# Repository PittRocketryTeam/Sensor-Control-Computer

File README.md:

# Sensor-Control-Computer
Code and design files for the Sensor and Control Avionics (SCA).

-`/hardware` contains Eagle schematics for SCA<br>
-`/software` contains software for SCA<br>

Current sensors:

- GPS: [Adafruit Ultimate GPS Breakout](https://www.adafruit.com/product/746) <br>
- Altimeter: [Adafruit BMP388](https://www.adafruit.com/product/3966) <br>
- IMU: [Adafruit 9-DOF Absolute Orientation IMU Fusion Breakout - BNO055](https://www.adafruit.com/product/2472) <br>
- Photocell: [CdS Photoresistor](https://www.adafruit.com/product/161) <br>
- Transceiver: [XBee Pro 900 HP](https://www.digikey.com/catalog/en/partgroup/xbee-pro-900hp/33082) <br>

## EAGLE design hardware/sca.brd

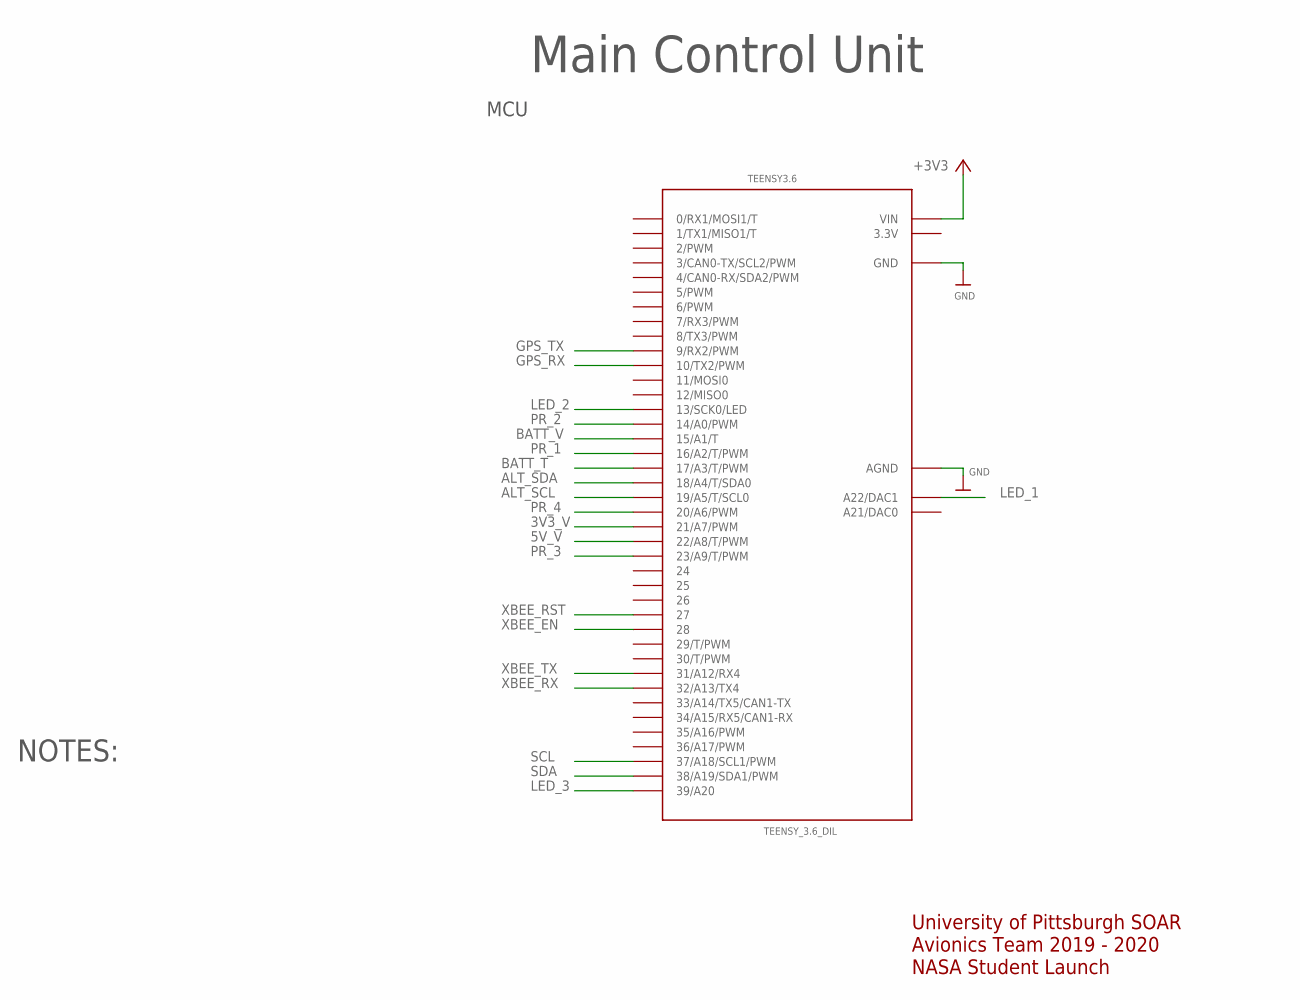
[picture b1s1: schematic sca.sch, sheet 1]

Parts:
TEENSY3.6: TEENSY_3.6_DIL

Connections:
3.3V: TEENSY3.6.3.3V, TEENSY3.6.3.3V3 (3.3V)
3V3_V: TEENSY3.6.21/A7 (21/A7/PWM); also elsewhere on the board
5V_V: TEENSY3.6.22/A8 (22/A8/T/PWM); also elsewhere on the board
+3V3: TEENSY3.6.VIN; also elsewhere on the board
ALT_SCL: TEENSY3.6.19/A5 (19/A5/T/SCL0); also elsewhere on the board
ALT_SDA: TEENSY3.6.18/A4 (18/A4/T/SDA0); also elsewhere on the board
BATT_T: TEENSY3.6.17/A3 (17/A3/T/PWM); also elsewhere on the board
BATT_V: TEENSY3.6.15/A1 (15/A1/T); also elsewhere on the board
GND: TEENSY3.6.AGND, TEENSY3.6.GND, TEENSY3.6.GND1 (GND); also elsewhere on the board
GPS_RX: TEENSY3.6.10 (10/TX2/PWM); also elsewhere on the board
GPS_TX: TEENSY3.6.9 (9/RX2/PWM); also elsewhere on the board
LED_1: TEENSY3.6.A22 (A22/DAC1); also elsewhere on the board
LED_2: TEENSY3.6.13 (13/SCK0/LED); also elsewhere on the board
LED_3: TEENSY3.6.39/A20; also elsewhere on the board
PR_1: TEENSY3.6.16/A2 (16/A2/T/PWM); also elsewhere on the board
PR_2: TEENSY3.6.14/A0 (14/A0/PWM); also elsewhere on the board
PR_3: TEENSY3.6.23/A9 (23/A9/T/PWM); also elsewhere on the board
PR_4: TEENSY3.6.20/A6 (20/A6/PWM); also elsewhere on the board
SCL: TEENSY3.6.37/A18 (37/A18/SCL1/PWM); also elsewhere on the board
SDA: TEENSY3.6.38/A19 (38/A19/SDA1/PWM); also elsewhere on the board
XBEE_EN: TEENSY3.6.28; also elsewhere on the board
XBEE_RST: TEENSY3.6.27; also elsewhere on the board
XBEE_RX: TEENSY3.6.32/A13 (32/A13/TX4); also elsewhere on the board
XBEE_TX: TEENSY3.6.31/A12 (31/A12/RX4); also elsewhere on the board

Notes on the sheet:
University of Pittsburgh SOAR Avionics Team 2019 - 2020 NASA Student Launch
NOTES:
Main Control Unit
MCU

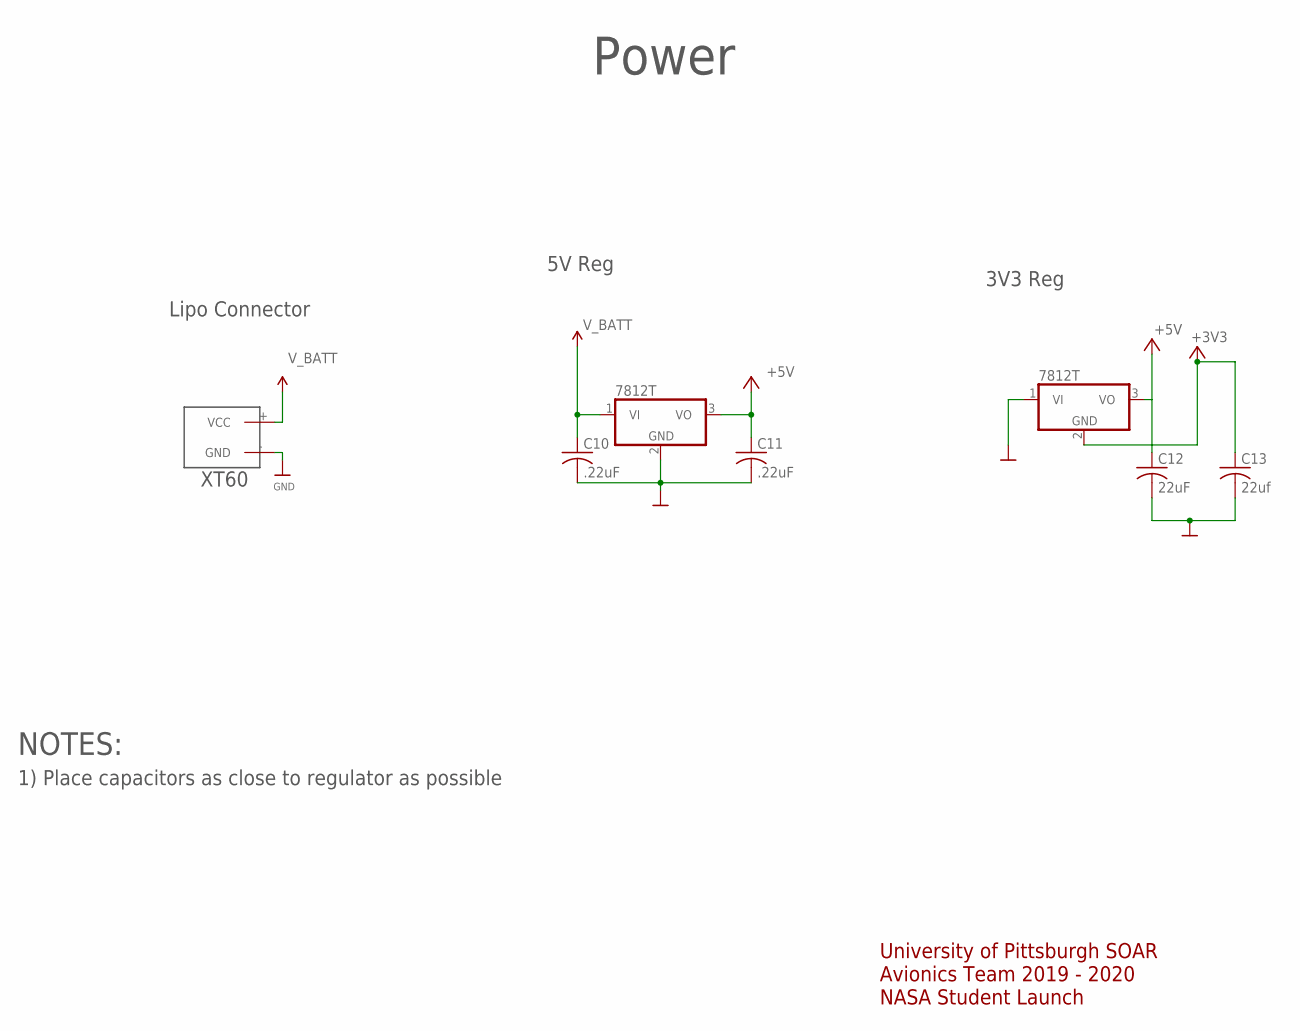
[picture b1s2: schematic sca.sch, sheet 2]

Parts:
3V3_REG, 5V_REG: 7812T; TO220H
C10, C11: .22uF; C025-040X050
C12: 22uF; C025-040X050
C13: 22uf; C025-040X050
U$5: XT60

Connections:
+3V3: 3V3_REG.2 (GND), C13.1; also elsewhere on the board
+5V: 3V3_REG.3 (VO), 5V_REG.3 (VO), C11.1, C12.1; also elsewhere on the board
GND: 3V3_REG.1 (VI), 5V_REG.2 (GND), C10.2, C11.2, C12.2, C13.2, U$5.- (GND); also elsewhere on the board
V_BATT: 5V_REG.1 (VI), C10.1, U$5.+ (VCC); also elsewhere on the board

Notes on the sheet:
Power
NOTES:
1) Place capacitors as close to regulator as possible
University of Pittsburgh SOAR Avionics Team 2019 - 2020 NASA Student Launch
Lipo Connector
5V Reg
3V3 Reg

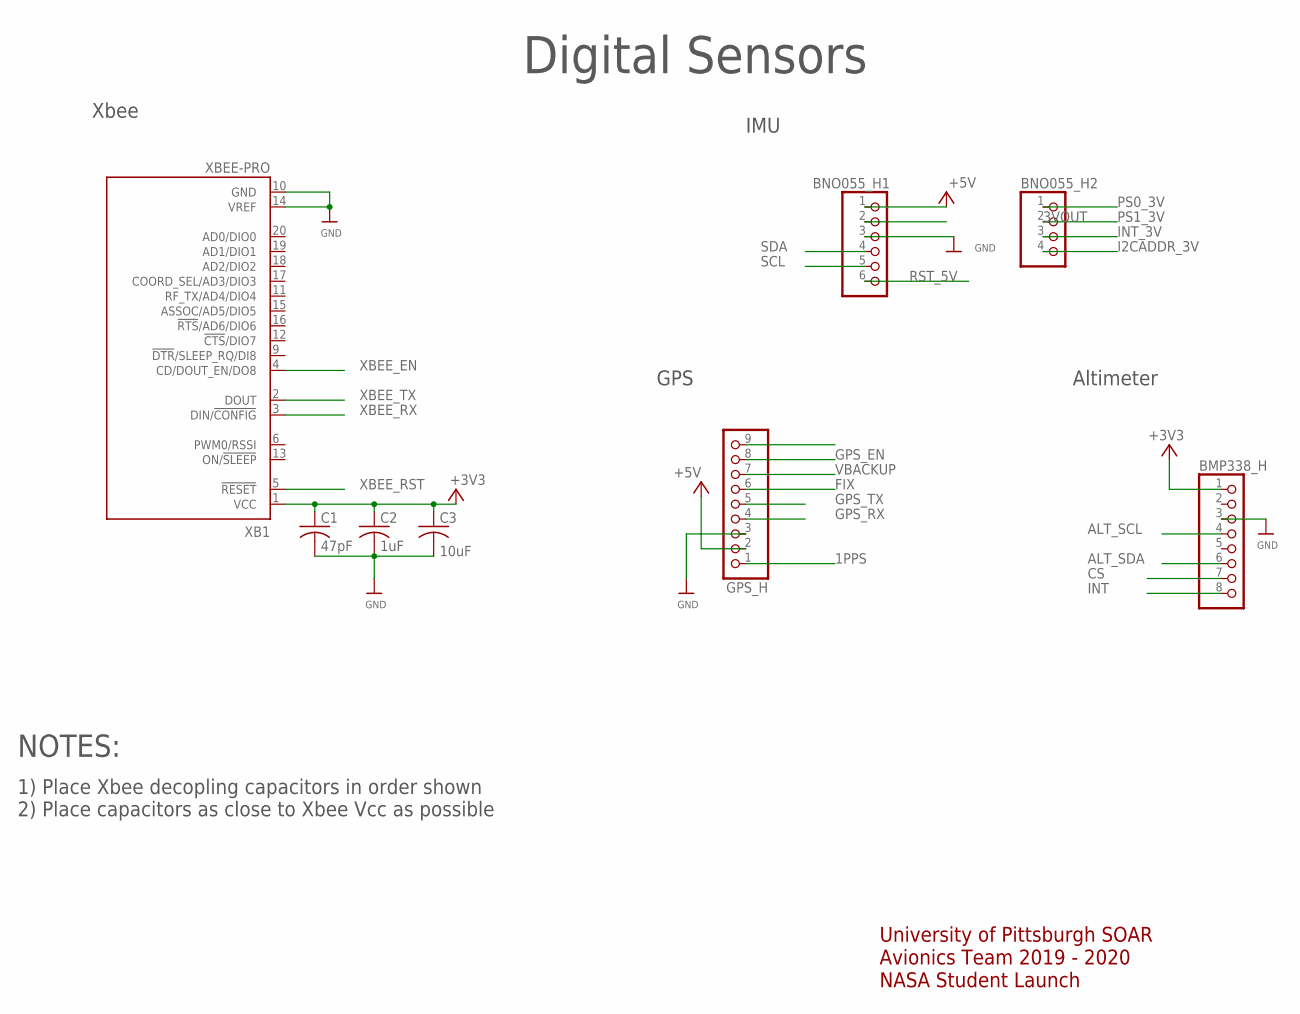
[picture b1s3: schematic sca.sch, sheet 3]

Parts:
BMP338_H: HEADER-1X870MIL; 1X08_ROUND_70
BNO055_H1: HEADER-1X676MIL; 1X06_ROUND_76
BNO055_H2: HEADER-1X476MIL; 1X04_ROUND_76
C1: 47pF; C025-040X050
C2: 1uF; C025-040X050
C3: 10uF; C025-040X050
GPS_H: HEADER-1X970MIL; 1X09_ROUND_70
XB1: XBEE-PRO

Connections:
1PPS: GPS_H.1
3VOUT: BNO055_H1.2
+3V3: BMP338_H.1, C1.1, C2.1, C3.1, XB1.1 (VCC); also elsewhere on the board
+5V: BNO055_H1.1, GPS_H.2; also elsewhere on the board
ALT_SCL: BMP338_H.4; also elsewhere on the board
ALT_SDA: BMP338_H.6; also elsewhere on the board
CS: BMP338_H.7
FIX: GPS_H.6
GND: BMP338_H.3, BNO055_H1.3, C1.2, C2.2, C3.2, GPS_H.3, XB1.10 (GND), XB1.14 (VREF); also elsewhere on the board
GPS_EN: GPS_H.8
GPS_RX: GPS_H.4; also elsewhere on the board
GPS_TX: GPS_H.5; also elsewhere on the board
I2CADDR_3V: BNO055_H2.4
INT: BMP338_H.8
INT_3V: BNO055_H2.3
PS0_3V: BNO055_H2.1
PS1_3V: BNO055_H2.2
RST_5V: BNO055_H1.6
SCL: BNO055_H1.5; also elsewhere on the board
SDA: BNO055_H1.4; also elsewhere on the board
VBACKUP: GPS_H.7
XBEE_EN: XB1.4 (CD/DOUT_EN/DO8); also elsewhere on the board
XBEE_RST: XB1.5 (!RESET); also elsewhere on the board
XBEE_RX: XB1.3 (DIN/!CONFIG); also elsewhere on the board
XBEE_TX: XB1.2 (DOUT); also elsewhere on the board

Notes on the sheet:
Digital Sensors
NOTES:
1) Place Xbee decopling capacitors in order shown 2) Place capacitors as close to Xbee Vcc as possible
University of Pittsburgh SOAR Avionics Team 2019 - 2020 NASA Student Launch
Xbee
IMU
GPS
Altimeter

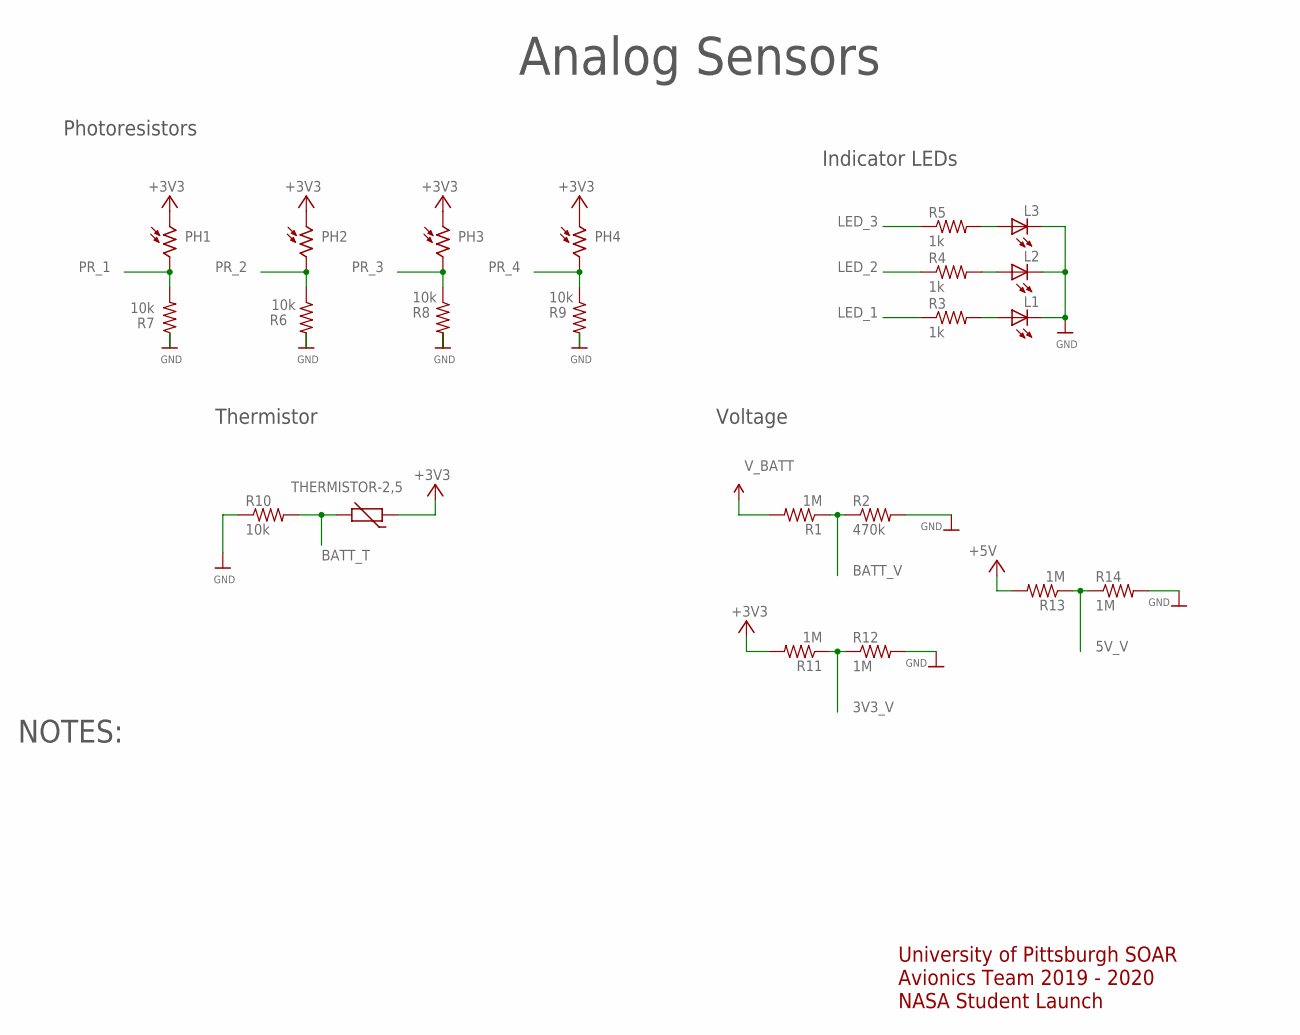
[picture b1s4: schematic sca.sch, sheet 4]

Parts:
L1, L2, L3: LED3MM
PH1, PH2, PH3, PH4: A1050_09; T0-46-A10XX
R1, R11, R12, R13, R14: 1M; 0309/10
R2: 470k; 0309/10
R3, R4, R5: 1k; 0309/10
R6, R7, R8, R9, R10: 10k; 0309/10
R20: THERMISTOR-2,5; RS-2,5

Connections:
3V3_V: R11.1, R12.1; also elsewhere on the board
5V_V: R13.1, R14.1; also elsewhere on the board
+3V3: PH1.1, PH2.1, PH3.1, PH4.1, R11.2, R20.1; also elsewhere on the board
+5V: R13.2; also elsewhere on the board
BATT_T: R10.2, R20.2; also elsewhere on the board
BATT_V: R1.1, R2.1; also elsewhere on the board
GND: L1.K (C), L2.K (C), L3.K (C), R2.2, R6.2, R7.1, R8.2, R9.2, R10.1, R12.2, R14.2; also elsewhere on the board
LED_1: R3.1; also elsewhere on the board
LED_2: R4.1; also elsewhere on the board
LED_3: R5.1; also elsewhere on the board
unnamed: L1.A, R3.2
unnamed: L2.A, R4.2
unnamed: L3.A, R5.2
PR_1: PH1.2, R7.2; also elsewhere on the board
PR_2: PH2.2, R6.1; also elsewhere on the board
PR_3: PH3.2, R8.1; also elsewhere on the board
PR_4: PH4.2, R9.1; also elsewhere on the board
V_BATT: R1.2; also elsewhere on the board

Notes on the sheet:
Analog Sensors
NOTES:
University of Pittsburgh SOAR Avionics Team 2019 - 2020 NASA Student Launch
Photoresistors
Thermistor
Voltage
Indicator LEDs

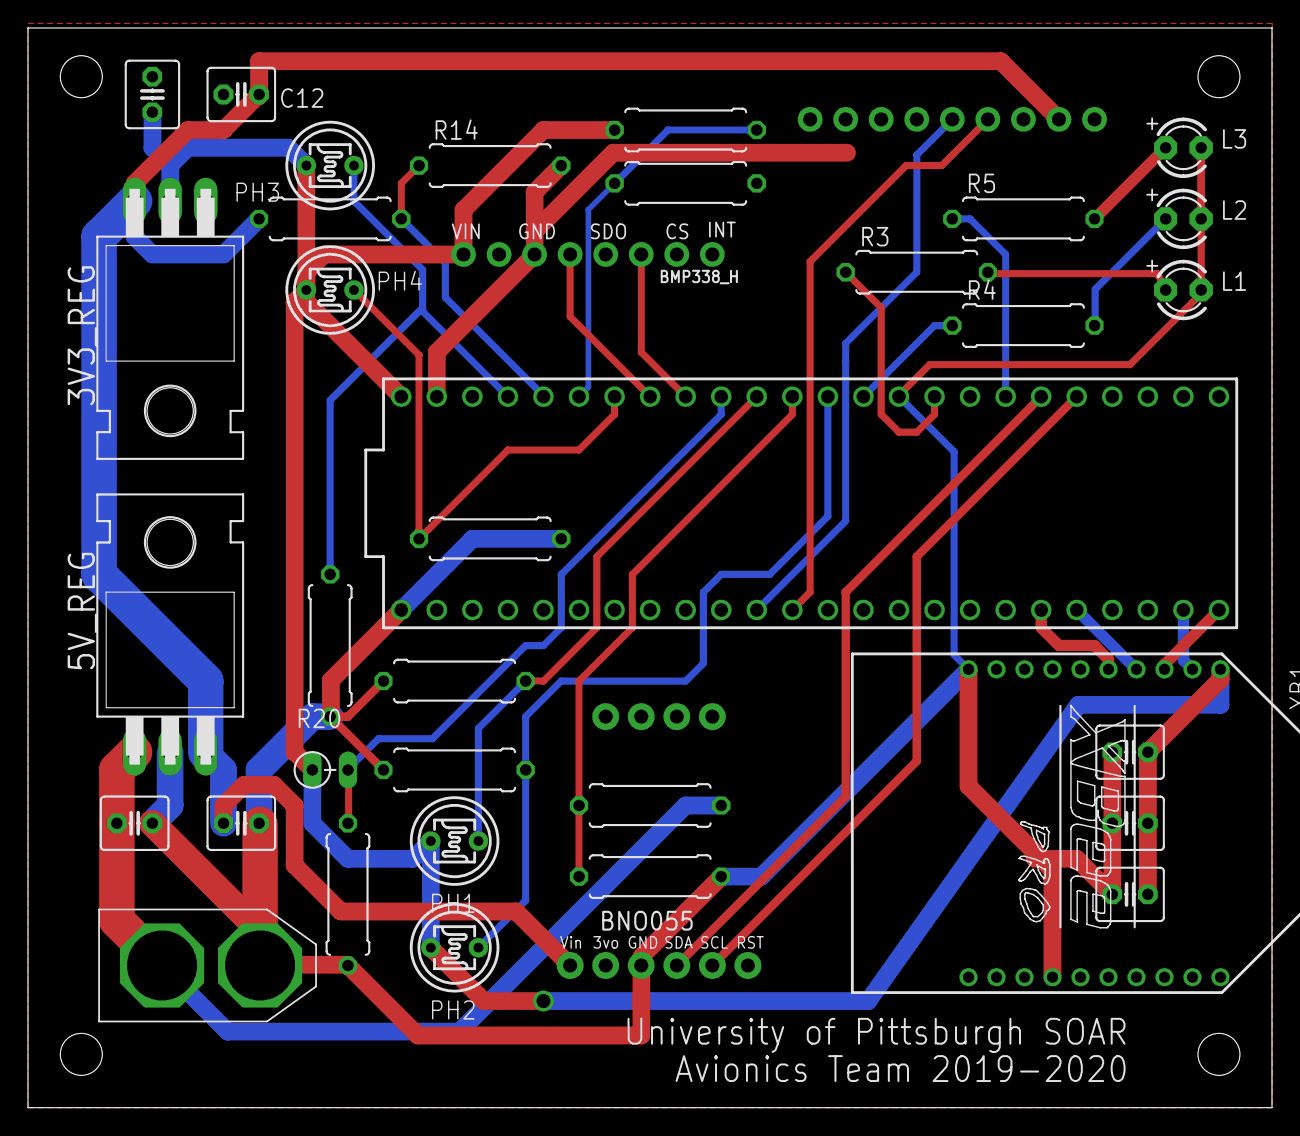
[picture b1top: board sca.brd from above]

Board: 2 copper layers, 88.9 x 77.1 mm, 38 parts (1 on the bottom side), 29 nets.

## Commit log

2019-09-23 add platformio project structure
2019-09-23 Updated readme and gitignore
2019-09-23 Moved existing software to software directory and created hardware directory
2019-09-23 moved autogenerated ci yaml file to /software
2019-09-29 Added schematic with teensy 3.6, XBee, BNO055 imu, Adafruit breakout GPS, and voltage dividers
2019-09-29 Added 4x photoresistors
2019-09-29 Added bmp388
2019-09-29 added thermistor circuit
2019-10-01 Created initial project structure as per inheritance meeting on sept 29
2019-10-01 Added source files for other components
2019-10-01 Made Sensor class functions non-pure so logger can add sensor-derived objects to collection of loggers
2019-10-01 Made logger functions non-pure (logger should be instantiable) and made addSensor use pass-by-pointer
2019-10-01 Fixed include guards
2019-10-01 Outlined remaining sensor and transceiver classes
2019-10-02 Added c++11 build flag, added GPS class, renamed transceiver write function to transmit and read function to receive
2019-10-03 Consolidated breakouts and added LEDs and battery voltage circuit
2019-10-03 added frame and cleaned up
2019-10-03 forgot to save last time
2019-10-03 added XT60 connector
2019-10-03 started power routing
2019-10-04 added thermistor routing
2019-10-06 add super constructor calls
2019-10-06 joe branch from master
2019-10-06 add metro library
2019-10-06 add atmega2560 env and implement health class
2019-10-07 Added data structs for altimeter, GPS, IMU, and photocell
2019-10-07 Removed unnecessary globals and created health class
2019-10-07 Resolve Health.cpp merge and updated readme with sensors
2019-10-07 Readme.md
2019-10-07 Changed vectors to structs; created preliminary logger class
2019-10-09 getting readings from sensor, testing different readings
2019-10-09 Changed SD to SdFat (faster logging), updated sensor functions to edit a struct rather than creating a new data struct, and added comments in sensor implementing classes to define what to do
2019-10-10 Added health data struct
2019-10-10 made changes discussed on Sunday
    temp sensor to 3V3
    photoresistors to 3V3
2019-10-10 Adding Adafruit Altimeter Library
2019-10-10 lots of layout changes
    updated teensy footprint to get rid of internal pins and pads
2019-10-11 Added EAGLE auto save and job file extensions
2019-10-11 missed one
2019-10-11 initial routing / changed xbee tx/rx for routing reasons
2019-10-11 Created a new function; added the 'setBaslinePressure' to the class file
2019-10-11 routing...
2019-10-11 Filled init, read, and baseline pressure(ground pressure)
2019-10-11 preliminary routing done
    adjusted some pins to optimize routing
2019-10-11 quick and dirty examples
2019-10-11 get_raw
2019-10-11 Updated poll() to just read the data
2019-10-11 implement Health and more examples
2019-10-11 cleaned up metro and added a few features
2019-10-12 Filled the enable, disable functions, and edited the read function so it wouldn't call 'performReading' twice
2019-10-12 fixed missed trace
2019-10-12 Added LoRa library
2019-10-13 Removed LoRa libary
2019-10-13 removed IMU 3V3 output
2019-10-13 added Xbee EN and Vref
2019-10-13 Added Decoupling Caps for Xbee per datasheet
2019-10-13 added notes
2019-10-13 added 3.3 and 5 V dividers
2019-10-13 Updated PDF
2019-10-13 Enable and disable
2019-10-13 Filled in init(), receive(),transmit(),enable(), and disable()
2019-10-13 spadinja/LoRaTransceiver: Minor change to enable()
2019-10-13 Added wait for serial and monitor_speed in platform.ini
2019-10-13 Updated poll() to return current data values
2019-10-13 Changed the struct to a struct pointer to avoid errors
2019-10-13 Fixed syntax
2019-10-13 Added private variables
2019-10-13 Fixed errors
2019-10-13 work on temp and fix metro
2019-10-13 corrected analog output pins
2019-10-13 Improved spacing
2019-10-13 LoRa class filled
2019-10-13 Commented out stuff in photocell so that it complies
2019-10-13 Commented out unused variables
2019-10-13 updated resistor values
2019-10-14 made power traces 50 mil min
2019-10-14 added team name
2019-10-15 updates to documentation files
2019-10-16 better names and debug led class
2019-10-16 updated via size and added copper pour
2019-10-17 Scrapped timer interrupts
2019-10-18 minor tweak
2019-10-18 updated power trace
2019-10-18 add newline
2019-10-18 Added destructors and changed the while(!serial) in main to a for loop so no infinite loops
2019-10-18 fixed gps pin orientation
2019-10-18 fix for null filename bug
2019-10-18 Altimeter data updates successfully and prints to the serial
2019-10-18 err codes
2019-10-20 Added Xbee library
2019-10-24 updated 3V3 regulator
2019-10-24 Filled in methods for XbeePro class
2019-10-27 Working on getting logging to not just log gibberish
2019-10-27 Fixed include
2019-10-27 added library
2019-10-27 added bno library
2019-10-29 Changed how struct Data is being sent.
2019-10-31 Revised Sensor interface with updated description of poll() vs. read()
2019-10-31 Updated comments
2019-11-03 Parsing test
2019-11-05 fixed gps class
2019-11-05 weird fix but ok
2019-11-12 Just commented out unused code
2019-11-14 Updated to match working version from subscale-telemetry repo
2019-11-14 Updated main from subscale-telemetry (I promise I will eventually implement git modules up in here)
2019-11-14 Commented out analogdevices
2019-11-14 Added board.hpp
2019-11-16 small fix
2019-11-17 Logger class now uses the teensy's RTC to name the logfile and to timestamp the logged data'
2019-11-17 Changed xbee communication
2019-11-17 work on error class
2019-11-28 finishing touches before review
2019-11-29 Pololu 5V Regulator
2019-12-14 add more error checking
2020-01-12 test GPS class
2020-01-12 add error codes to gps
2020-01-19 Changed a couple of xbee objects and data will be sent to a different address in the XBeePro.hpp and XBeePro.cpp files. *This code still needs to be tested*
2020-01-19 the one with the 55 in it
2020-01-19 Added XBee library for transmitting Data struct as string
2020-01-19 latest changes
2020-01-24 Changes -- found the SL addresses for the xbee modules. Changed the Xbee.cpp and Xbee.hpp to XbeeP.cpp and XbeeP.hpp so the Xbee arduino libraries can be used
2020-01-24 some stuff to test
2020-01-24 No more xbee arduino code.
2020-01-24 No more LoRa code.
2020-02-02 stuff
2020-02-02 it's working
2020-02-06 manufactured boards
2020-02-07 integrate health class
2020-02-08 latest
2020-02-09 fixed battery reading
2020-02-11 gerbers and updates
2020-02-14 Fixed the altitude readings by setting baseline pressure from sea level
2020-02-14 majoooor style refactoring
2020-02-14 fixed gps and improved stability
2020-02-19 cleanup
2020-02-25 back to loggylog.log
2020-02-29 unique filenames should work
2020-02-29 i forgot something

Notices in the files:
parts and their libraries:
SparkFun-PowerSymbols: Licensing: Creative Commons ShareAlike 4.0 International - https://creativecommons.org/licenses/by-sa/4.0
